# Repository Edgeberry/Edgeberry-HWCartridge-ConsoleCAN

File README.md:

The Edgeberry **Console & CAN Hardware Cartridge** allows you to use your Edgeberry device in a wide range of industrial applications. The CAN-bus is utilized in diverse fields, from medical equipment to heavy industrial machinery. Additionally, the USB interface provides access to your Raspberry Pi's console, enabling direct local control over your device.

<br clear="right"/>

## Usage

### Console
Configure your Raspberry Pi to enable console access on the UART with `raspi-config`, or by manually adding following lines the boot configuration file `/boot/firmware/config.txt`:
```
enable_uart=1
dtparam=uart0
dtparam=uart0_console
```
Now `reboot` the device to apply these settings.

Connect to your Edgeberry device with your computer system, and open a terminal emulation program (e.g. minicom, PuTTY) with the following settings
```
Speed: 115200 baud
Bits: 8
Parity: None
Stop Bits: 1
Flow Control: None
```
If this went well, you now have access to your Edgeberry's console.

### CAN-bus
To enable the CAN interface, add the following lines the boot configuration file `/boot/firmware/config.txt`:
```
# CAN interface
dtoverlay=mcp2515-can0,oscillator=16000000,interrupt=25
```
And reboot your device. After rebooting, set up the CAN interface 
```
sudo ip link set can0 up type can bitrate 500000
```
Now you can see the `can0` interface when running `ifconfig`.

#### Resources
https://github.com/iDoka/awesome-canbus<br/>
https://www.beyondlogic.org/adding-can-controller-area-network-to-the-raspberry-pi/<br/>
https://www.hackster.io/youness/how-to-connect-raspberry-pi-to-can-bus-b60235<br/>
http://lnxpps.de/rpie/

## License & Collaboration
**Copyright© 2024 Sanne 'SpuQ' Santens**. This project is released under the **CERN OHL-W** license. The [Rules & Guidelines](https://github.com/Edgeberry/.github/blob/main/brand/Edgeberry_Trademark_Rules_and_Guidelines.md) apply to the usage of the Edgeberry™ brand.

### Collaboration

If you'd like to contribute to this project, please follow these guidelines:
1. Fork the repository and create your branch from `main`.
2. Make your changes and ensure they adhere to the project's design style and conventions.
3. Test your changes thoroughly.
4. Ensure your commits are descriptive and well-documented.
5. Open a pull request, describing the changes you've made and the problem or feature they address.

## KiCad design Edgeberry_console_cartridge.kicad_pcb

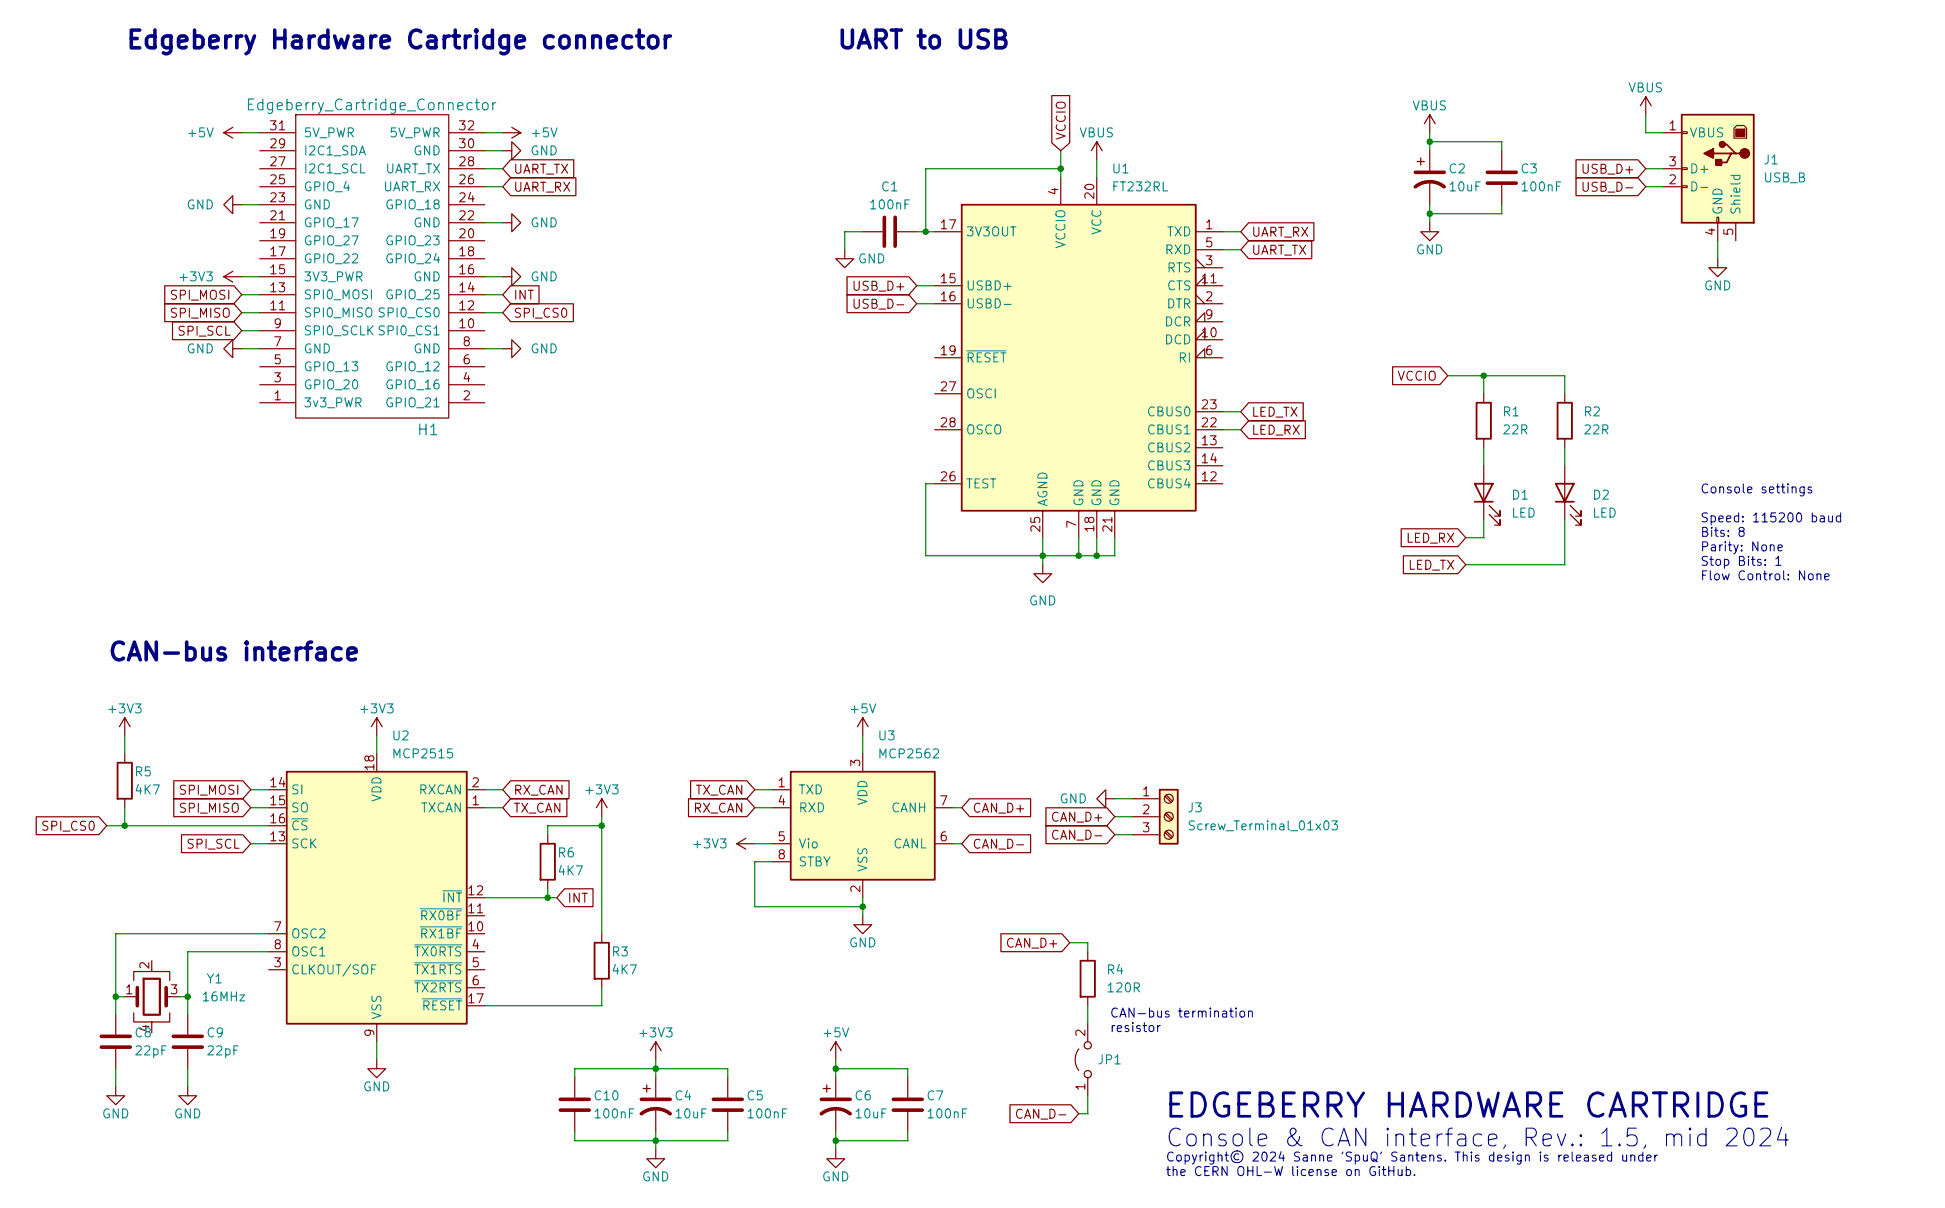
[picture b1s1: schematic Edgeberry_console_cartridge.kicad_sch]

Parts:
C1, C3, C5, C7, C10: 100nF; C_0805_2012Metric
C2, C4, C6: 10uF; CP_Elec_4x5.4
C8, C9: 22pF; C_0805_2012Metric
D1, D2: LED; LED_0805_2012Metric
H1: Edgeberry_Cartridge_Connector; PinHeader_2x16_P2.54mm_Horizontal
J1: USB_B; USB_B_OST_USB-B1HSxx_Horizontal
J3: Screw_Terminal_01x03; PhoenixContact_MSTBA_2,5_3-G-5,08_1x03_P5.08mm_Horizontal
JP1: Jumper_2_Open; PinHeader_1x02_P2.54mm_Vertical
R1, R2: 22R; R_0805_2012Metric
R3, R5, R6: 4K7; R_0805_2012Metric
R4: 120R; R_0805_2012Metric
U1: FT232RL; SSOP-28_5.3x10.2mm_P0.65mm
U2: MCP2515; SOIC-18W_7.5x11.6mm_P1.27mm
U3: MCP2562; SOIC-8_3.9x4.9mm_P1.27mm
Y1: 16MHz; Crystal_SMD_3225-4Pin_3.2x2.5mm

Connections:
+3V3: C4.1, C5.1, C10.1, H1.15 (3V3_PWR), R3.1, R5.1, R6.1, U2.18 (VDD), U3.5 (Vio)
+5V: C6.1, C7.1, H1.31 (5V_PWR), H1.32 (5V_PWR), U3.3 (VDD)
CAN_D+: J3.2, R4.1, U3.7 (CANH)
CAN_D-: J3.3, JP1.1 (A), U3.6 (CANL)
GND: C1.1, C2.2, C3.2, C4.2, C5.2, C6.2, C7.2, C8.2, C9.2, C10.2, H1.6 (GPIO_12), H1.7 (GND), H1.8 (GND), H1.16 (GND), H1.22 (GND), H1.23 (GND), H1.30 (GND), J1.4 (GND), J3.1, U1.7 (GND), U1.18 (GND), U1.21 (GND), U1.25 (AGND), U1.26 (TEST), U2.9 (VSS), U3.2 (VSS), U3.8 (STBY)
INT: H1.14 (GPIO_25), R6.2, U2.12 (~INT)
LED_RX: D1.1 (K), U1.22 (CBUS1)
LED_TX: D2.1 (K), U1.23 (CBUS0)
unnamed: D1.2 (A), R1.2
unnamed: D2.2 (A), R2.2
unnamed: JP1.2 (B), R4.2
unnamed: C9.1, U2.8 (OSC1), Y1.3
unnamed: C8.1, U2.7 (OSC2), Y1.1
unnamed: R3.2, U2.17 (~RESET)
RX_CAN: U2.2 (RXCAN), U3.4 (RXD)
SPI_CS0: H1.12 (SPI0_CS0), R5.2, U2.16 (~CS)
SPI_MISO: H1.11 (SPI0_MISO), U2.15 (SO)
SPI_MOSI: H1.13 (SPI0_MOSI), U2.14 (SI)
SPI_SCL: H1.9 (SPI0_SCLK), U2.13 (SCK)
TX_CAN: U2.1 (TXCAN), U3.1 (TXD)
UART_RX: H1.26 (UART_RX), U1.1 (TXD)
UART_TX: H1.28 (UART_TX), U1.5 (RXD)
USB_D+: J1.3 (D+), U1.15 (USBD+)
USB_D-: J1.2 (D-), U1.16 (USBD-)
VBUS: C2.1, C3.1, J1.1 (VBUS), U1.20 (VCC)
VCCIO: C1.2, R1.1, R2.1, U1.4 (VCCIO), U1.17 (3V3OUT)

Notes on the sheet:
CAN-bus interface
EDGEBERRY HARDWARE CARTRIDGE
UART to USB
Console & CAN interface, Rev.: 1.5, mid 2024
Copyright© 2024 Sanne 'SpuQ' Santens. This design is released under the CERN OHL-W license on GitHub.
CAN-bus termination resistor
Edgeberry Hardware Cartridge connector
Console settings Speed: 115200 baud Bits: 8 Parity: None Stop Bits: 1 Flow Control: None

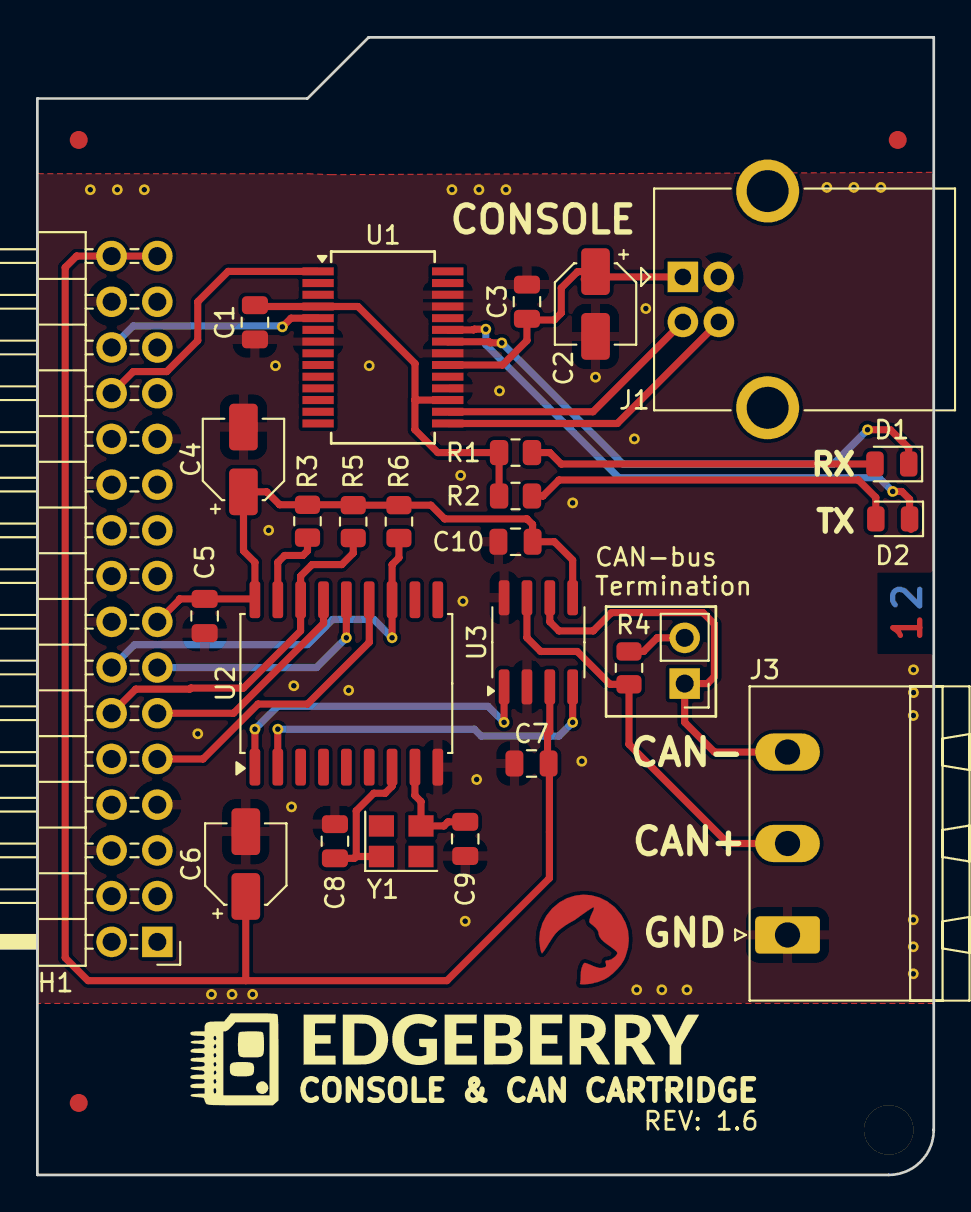
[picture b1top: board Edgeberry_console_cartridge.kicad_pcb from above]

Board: 2 copper layers, 49.8 x 63.2 mm, 26 parts (0 on the bottom side), 26 nets.

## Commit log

2024-05-15 Initial commit of the designs
2024-05-15 Added the gitignore file
2024-05-15 ReadMe: introduction improvement
2024-05-15 ReadMe: usage: console basics
2024-05-15 Documentation: better image of the cartridge
2024-05-15 ReadMe: better 'insert cartridge' image
2024-05-16 ReadMe: Console configuration instructions
2024-05-16 ReadMe: Console configuration & usage
2024-05-18 Update to KiCad 8 + footprint cleanup
2024-05-18 Silk screen improvements
2024-05-19 Open Source Hardware license: CERN-OHL-W
2024-05-22 ReadMe: image improvements
2024-06-25 ReadMe: Trademark Rules & Guidelines
2024-07-14 ReadMe: CAN interface usage
2024-07-15 ReadMe: CAN resources
2024-08-27 lock connector footprints
2024-08-27 Cartridge faceplate design
2024-08-29 Rendering with faceplate
2024-08-29 Faceplate: fix USB dimensions
2024-08-29 Cleanup
2024-08-29 ReadMe: introduction text improvement
2024-09-22 Tindie button
2024-11-01 Faceplate: power jack cutout
2024-12-08 Documentation: Schematic + Assembly
2024-12-08 Faceplate: optimization
2024-12-08 Documentation: remove banner
2024-12-08 ReadMe: update banner
2024-12-22 ReadMe: Remove Tindie link
2025-01-20 ReadMe: Enable UART for console
2025-03-16 uniformity
